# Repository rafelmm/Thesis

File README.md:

# Thesis
MERIT Thesis documents

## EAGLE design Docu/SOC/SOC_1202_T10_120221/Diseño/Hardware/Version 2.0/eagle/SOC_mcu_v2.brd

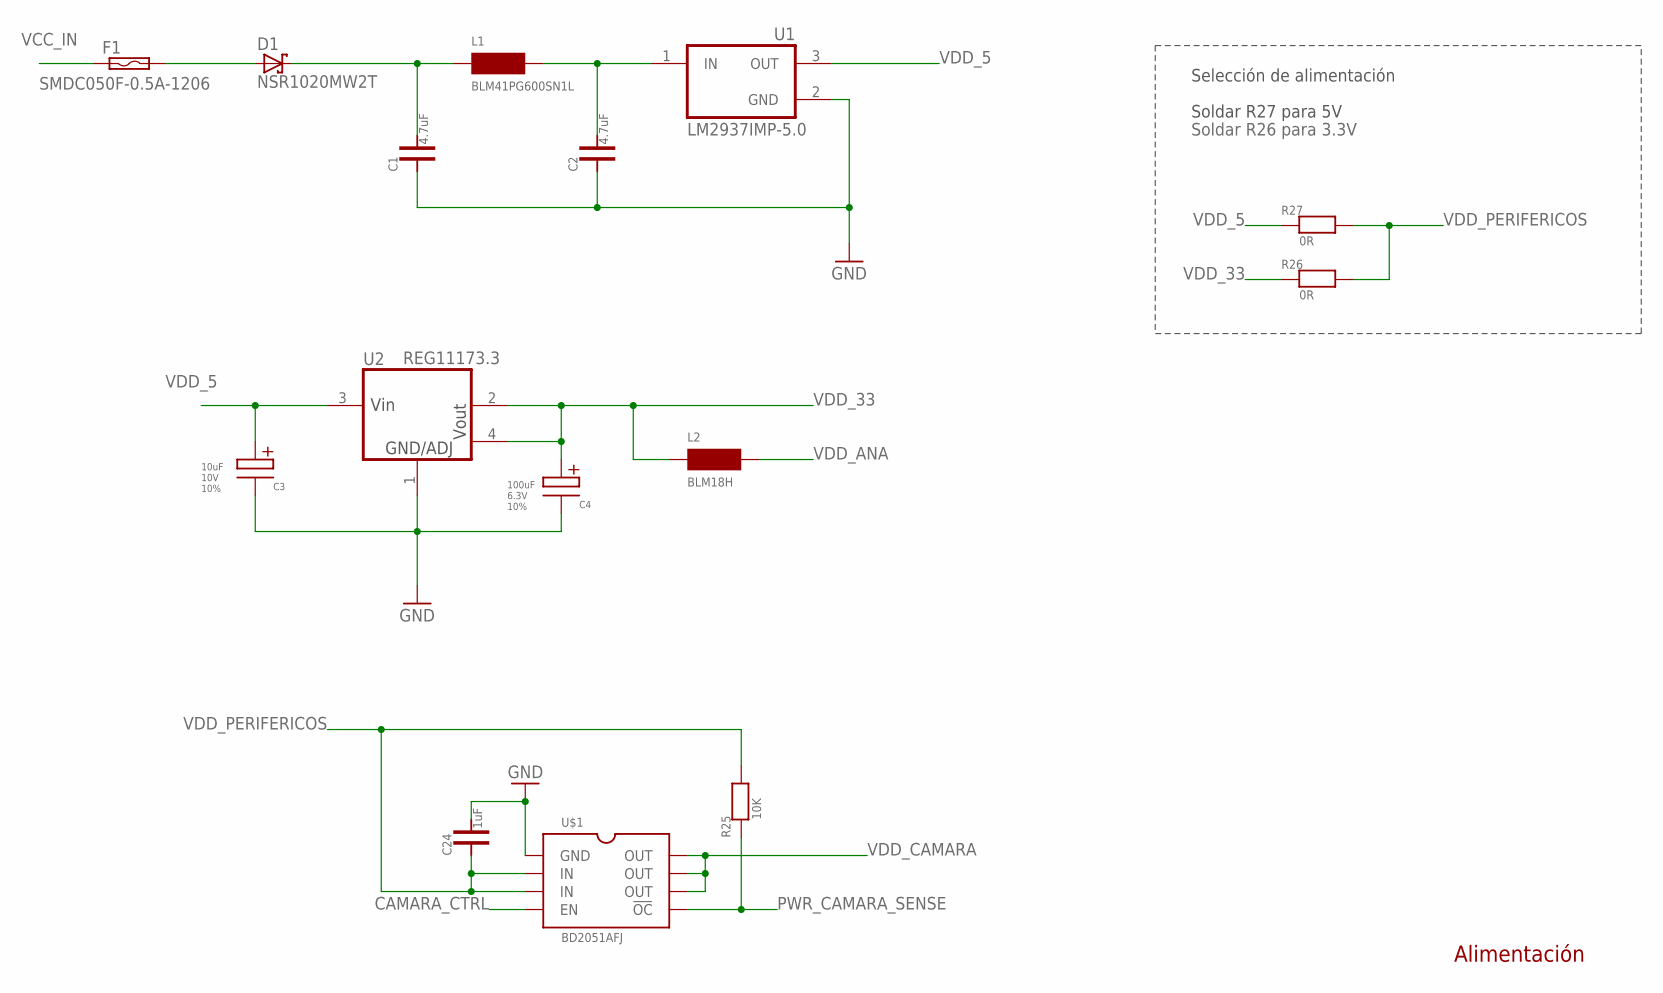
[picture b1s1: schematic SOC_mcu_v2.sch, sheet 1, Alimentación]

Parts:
C1, C2: 4.7uF; C0805
C3: 10uF; 3528-21
C4: 100uF; 3528-21
C24: 1uF; C0402
D1: NSR1020MW2T; SOD323
F1: SMDC050F-0.5A-1206; 1206; MPN NANOSMDC050F/13.2
L1: BLM41PG600SN1L; 1806
L2: BLM18H; 0603
R25: 10K; R0402
R26, R27: 0R; R0402
U1: LM2937IMP-5.0; SOT223
U2: REG11173.3; SOT223
U$1: BD2051AFJ; SO08

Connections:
CAMARA_CTRL: U$1.4 (EN); also elsewhere on the board
GND: C1.1, C2.1, C3.NEG, C4.NEG, C24.2, U1.2 (GND), U1.4 (GND), U2.1 (GND), U$1.1 (GND); also elsewhere on the board
unnamed: C2.2, L1.P$2 (2), U1.1 (IN)
unnamed: C1.2, D1.C, L1.P$1 (1)
unnamed: D1.A, F1.2
PWR_CAMARA_SENSE: R25.1, U$1.5 (!OC); also elsewhere on the board
VCC_IN: F1.1; also elsewhere on the board
VDD_5: C3.POS, R27.1, U1.3 (OUT), U2.3 (VIN)
VDD_33: C4.POS, L2.1, R26.1, U2.2 (VOUT), U2.4 (VO2); also elsewhere on the board
VDD_ANA: L2.2; also elsewhere on the board
VDD_CAMARA: U$1.6 (OUT), U$1.7 (OUT), U$1.8 (OUT); also elsewhere on the board
VDD_PERIFERICOS: C24.1, R25.2, R26.2, R27.2, U$1.2 (IN), U$1.3 (IN); also elsewhere on the board

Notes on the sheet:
Alimentación
Selección de alimentación
Soldar R27 para 5V
Soldar R26 para 3.3V

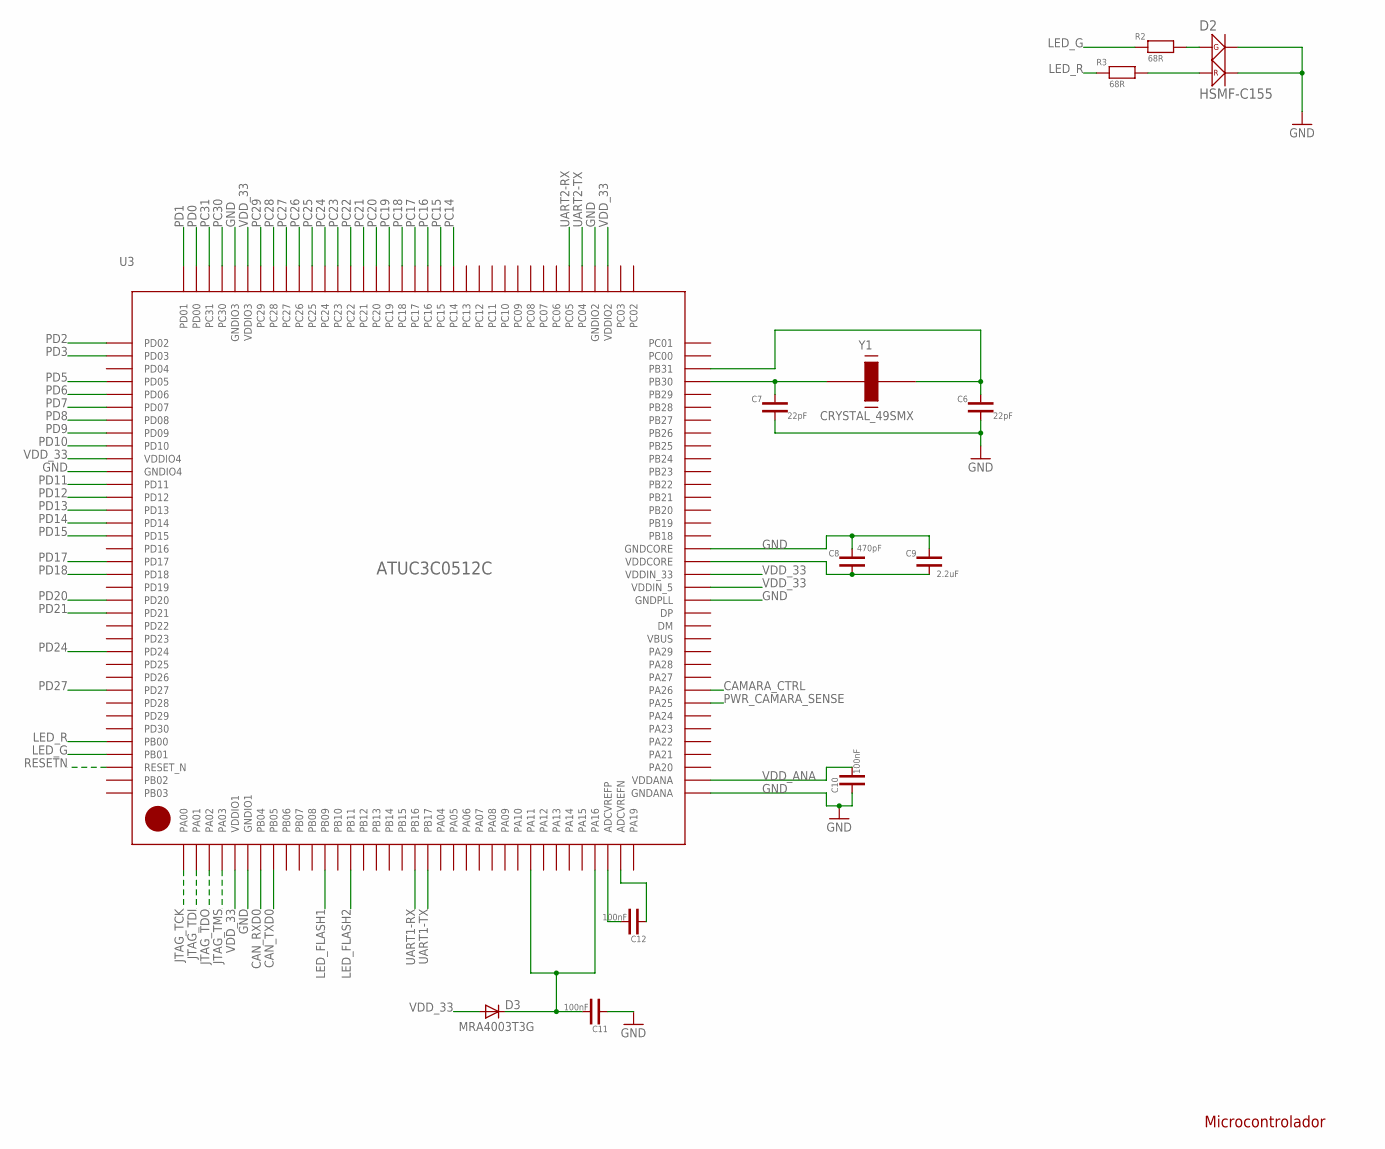
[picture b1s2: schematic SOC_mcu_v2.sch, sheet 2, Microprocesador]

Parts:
C6, C7: 22pF; C0402
C8: 470pF; C0402
C9: 2.2uF; C0603
C10, C11, C12: 100nF; C0402
D2: HSMF-C155; HSMF-C
D3: MRA4003T3G; SMA
R2, R3: 68R; R0402
U3: ATUC3C0512C; TQFP144
Y1: CRYSTAL_49SMX; HC49UP

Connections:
CAMARA_CTRL: U3.45 (PA26); also elsewhere on the board
CAN_RXD0: U3.7 (PB04); also elsewhere on the board
CAN_TXD0: U3.8 (PB05); also elsewhere on the board
GND: C6.1, C7.1, C8.2, C9.2, C10.1, C11.1, D2.2, D2.4, U3.6 (GNDIO1), U3.37 (GNDANA), U3.52 (GNDPLL), U3.56 (GNDCORE), U3.76 (GNDIO2), U3.104 (GNDIO3), U3.119 (GNDIO4); also elsewhere on the board
JTAG_TCK: U3.1 (PA00); also elsewhere on the board
JTAG_TDI: U3.2 (PA01); also elsewhere on the board
JTAG_TDO: U3.3 (PA02); also elsewhere on the board
JTAG_TMS: U3.4 (PA03); also elsewhere on the board
LED_FLASH1: U3.12 (PB09); also elsewhere on the board
LED_FLASH2: U3.14 (PB11); also elsewhere on the board
LED_G: R2.1, U3.141 (PB01)
LED_R: R3.1, U3.140 (PB00)
unnamed: C6.2, U3.70 (PB31), Y1.2
unnamed: C7.2, U3.69 (PB30), Y1.1
unnamed: C8.1, C9.1, U3.55 (VDDCORE)
unnamed: D2.1, R2.2
unnamed: D2.3, R3.2
unnamed: C11.2, D3.C, U3.28 (PA11), U3.33 (PA16)
unnamed: C12.2, U3.34 (ADCVREFP)
unnamed: C12.1, U3.35 (ADCVREFN)
PC14: U3.87 (PC14); also elsewhere on the board
PC15: U3.88 (PC15); also elsewhere on the board
PC16: U3.89 (PC16); also elsewhere on the board
PC17: U3.90 (PC17); also elsewhere on the board
PC18: U3.91 (PC18); also elsewhere on the board
PC19: U3.92 (PC19); also elsewhere on the board
PC20: U3.93 (PC20); also elsewhere on the board
PC21: U3.94 (PC21); also elsewhere on the board
PC22: U3.95 (PC22); also elsewhere on the board
PC23: U3.96 (PC23); also elsewhere on the board
PC24: U3.97 (PC24); also elsewhere on the board
PC25: U3.98 (PC25); also elsewhere on the board
PC26: U3.99 (PC26); also elsewhere on the board
PC27: U3.100 (PC27); also elsewhere on the board
PC28: U3.101 (PC28); also elsewhere on the board
PC29: U3.102 (PC29); also elsewhere on the board
PC30: U3.105 (PC30); also elsewhere on the board
PC31: U3.106 (PC31); also elsewhere on the board
PD0: U3.107 (PD00); also elsewhere on the board
PD1: U3.108 (PD01); also elsewhere on the board
PD2: U3.109 (PD02); also elsewhere on the board
PD3: U3.110 (PD03); also elsewhere on the board
PD5: U3.112 (PD05); also elsewhere on the board
PD6: U3.113 (PD06); also elsewhere on the board
PD7: U3.114 (PD07); also elsewhere on the board
PD8: U3.115 (PD08); also elsewhere on the board
PD9: U3.116 (PD09); also elsewhere on the board
PD10: U3.117 (PD10); also elsewhere on the board
PD11: U3.120 (PD11); also elsewhere on the board
PD12: U3.121 (PD12); also elsewhere on the board
PD13: U3.122 (PD13); also elsewhere on the board
PD14: U3.123 (PD14); also elsewhere on the board
PD15: U3.124 (PD15); also elsewhere on the board
PD17: U3.126 (PD17); also elsewhere on the board
PD18: U3.127 (PD18); also elsewhere on the board
PD20: U3.129 (PD20); also elsewhere on the board
PD21: U3.130 (PD21); also elsewhere on the board
PD24: U3.133 (PD24); also elsewhere on the board
PD27: U3.136 (PD27); also elsewhere on the board
PWR_CAMARA_SENSE: U3.44 (PA25); also elsewhere on the board
RESETN: U3.142 (RESET_N); also elsewhere on the board
UART1-RX: U3.19 (PB16); also elsewhere on the board
UART1-TX: U3.20 (PB17); also elsewhere on the board
UART2-RX: U3.78 (PC05); also elsewhere on the board
UART2-TX: U3.77 (PC04); also elsewhere on the board
VDD_33: D3.A, U3.5 (VDDIO1), U3.53 (VDDIN_5), U3.54 (VDDIN_33), U3.75 (VDDIO2), U3.103 (VDDIO3), U3.118 (VDDIO4); also elsewhere on the board
VDD_ANA: C10.2, U3.38 (VDDANA); also elsewhere on the board

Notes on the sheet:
Microcontrolador

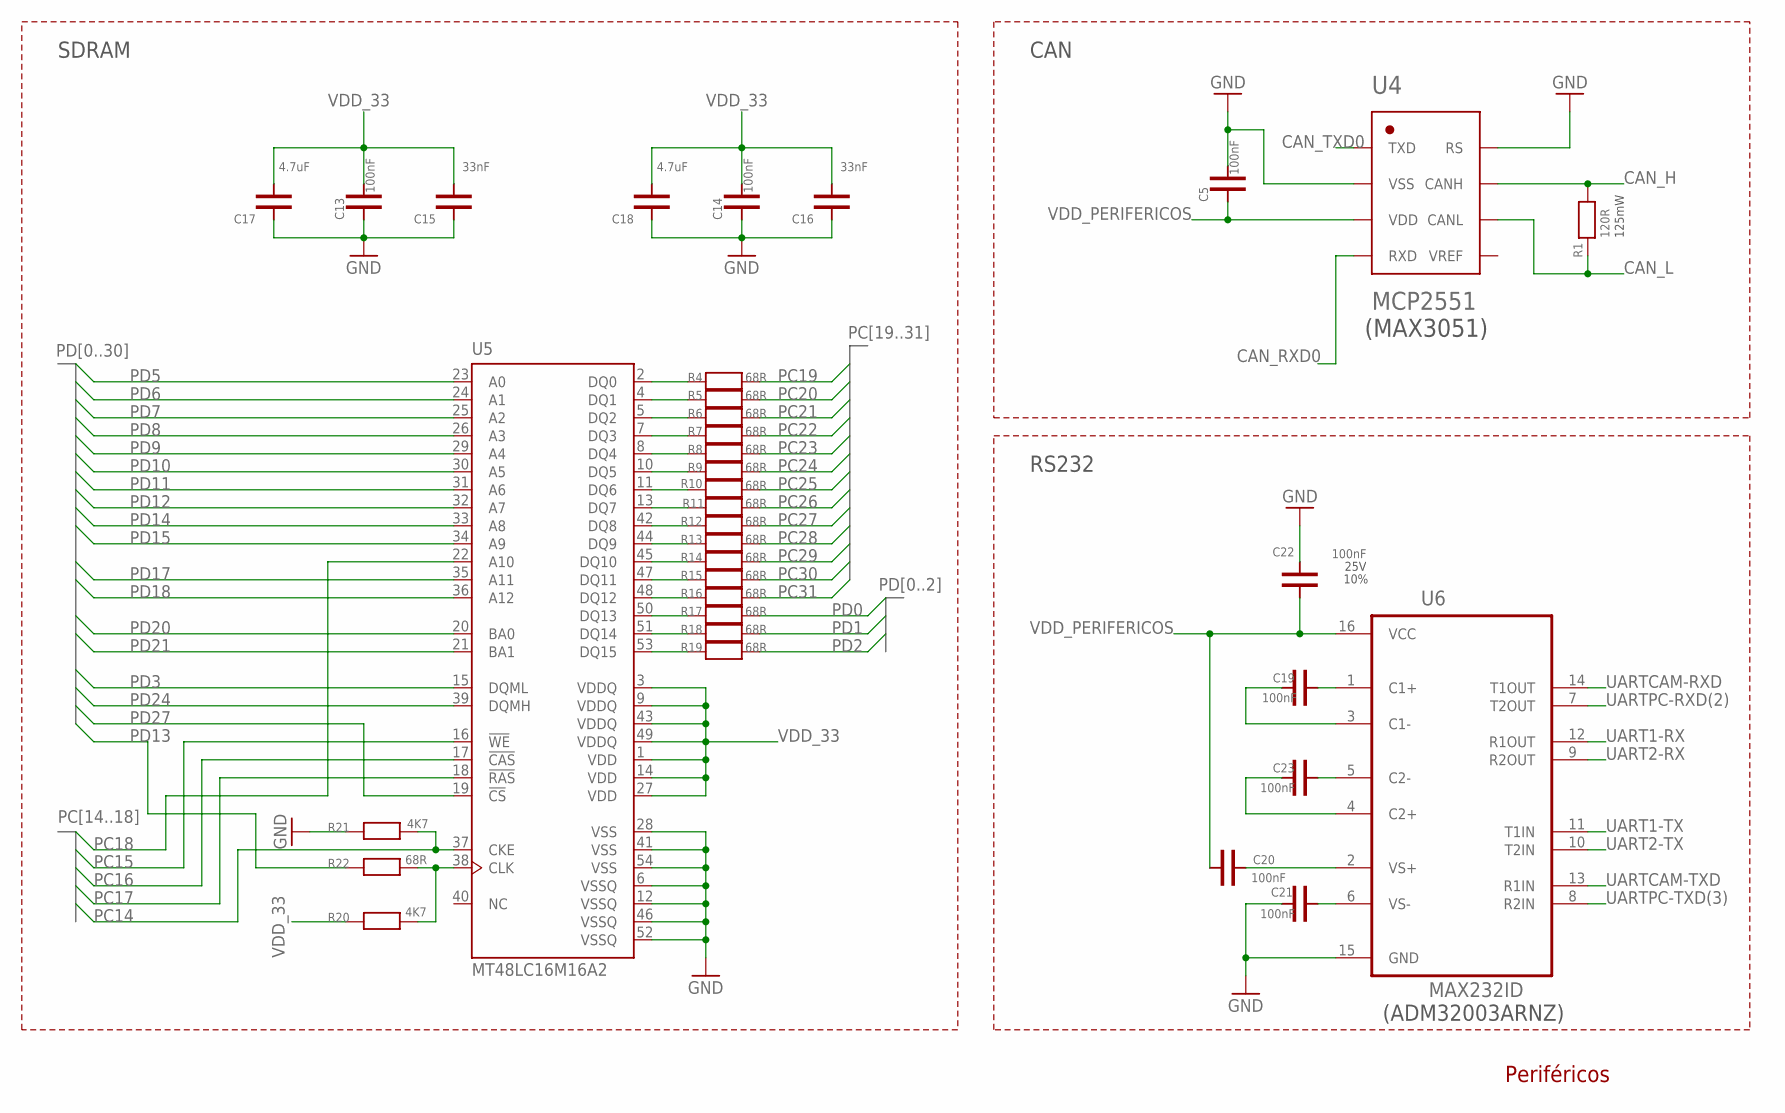
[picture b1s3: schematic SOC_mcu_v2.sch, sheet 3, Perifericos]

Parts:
C5, C13, C14: 100nF; C0402
C15, C16: 33nF; C0402; TOLERANCE 10%; VOLTAGE 25V
C17, C18: 4.7uF; C0805; TOLERANCE 10%; VOLTAGE 16V
C19, C20, C21, C22, C23: 100nF; C0402; TOLERANCE 10%; VOLTAGE 25V
R1: 120R; R0402; TOLERANCE 1%
R4, R5, R6, R7, R8, R9, R10, R11, R12, R13, R14, R15, R16, R17, R18, R19, R22: 68R; R0402; TOLERANCE 5%
R20, R21: 4K7; R0402; TOLERANCE 1%
U4: MCP2551; SO08
U5: MT48LC16M16A2; TSOP54-400
U6: MAX232ID; SOIC127P600X175-16N

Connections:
CAN_H: R1.2, U4.7 (CANH); also elsewhere on the board
CAN_L: R1.1, U4.6 (CANL); also elsewhere on the board
CAN_RXD0: U4.4 (RXD); also elsewhere on the board
CAN_TXD0: U4.1 (TXD); also elsewhere on the board
GND: C5.2, C13.1, C14.1, C15.1, C16.1, C17.1, C18.1, C21.1, C22.2, R21.1, U4.2 (VSS), U4.8 (RS), U5.6 (VSSQ), U5.12 (VSSQ), U5.28 (VSS), U5.41 (VSS), U5.46 (VSSQ), U5.52 (VSSQ), U5.54 (VSS), U6.15 (GND); also elsewhere on the board
unnamed: R4.1, U5.2 (DQ0)
unnamed: R5.1, U5.4 (DQ1)
unnamed: R6.1, U5.5 (DQ2)
unnamed: R7.1, U5.7 (DQ3)
unnamed: R8.1, U5.8 (DQ4)
unnamed: R9.1, U5.10 (DQ5)
unnamed: C19.2, U6.1 (C1+)
unnamed: R10.1, U5.11 (DQ6)
unnamed: R11.1, U5.13 (DQ7)
unnamed: R12.1, U5.42 (DQ8)
unnamed: R13.1, U5.44 (DQ9)
unnamed: R14.1, U5.45 (DQ10)
unnamed: R15.1, U5.47 (DQ11)
unnamed: R16.1, U5.48 (DQ12)
unnamed: R17.1, U5.50 (DQ13)
unnamed: R18.1, U5.51 (DQ14)
unnamed: R19.1, U5.53 (DQ15)
unnamed: R20.2, R22.2, U5.38 (CLK)
unnamed: C23.2, U6.5 (C2-)
unnamed: C19.1, U6.3 (C1-)
unnamed: C20.2, U6.2 (VS+)
unnamed: C23.1, U6.4 (C2+)
unnamed: C21.2, U6.6 (VS-)
PC14: R21.2, U5.37 (CKE); also elsewhere on the board
PC15: U5.16 (!WE); also elsewhere on the board
PC16: U5.17 (!CAS); also elsewhere on the board
PC17: U5.18 (!RAS); also elsewhere on the board
PC18: U5.22 (A10); also elsewhere on the board
PC19: R4.2; also elsewhere on the board
PC20: R5.2; also elsewhere on the board
PC21: R6.2; also elsewhere on the board
PC22: R7.2; also elsewhere on the board
PC23: R8.2; also elsewhere on the board
PC24: R9.2; also elsewhere on the board
PC25: R10.2; also elsewhere on the board
PC26: R11.2; also elsewhere on the board
PC27: R12.2; also elsewhere on the board
PC28: R13.2; also elsewhere on the board
PC29: R14.2; also elsewhere on the board
PC30: R15.2; also elsewhere on the board
PC31: R16.2; also elsewhere on the board
PD0: R17.2; also elsewhere on the board
PD1: R18.2; also elsewhere on the board
PD2: R19.2; also elsewhere on the board
PD3: U5.15 (DQML); also elsewhere on the board
PD5: U5.23 (A0); also elsewhere on the board
PD6: U5.24 (A1); also elsewhere on the board
PD7: U5.25 (A2); also elsewhere on the board
PD8: U5.26 (A3); also elsewhere on the board
PD9: U5.29 (A4); also elsewhere on the board
PD10: U5.30 (A5); also elsewhere on the board
PD11: U5.31 (A6); also elsewhere on the board
PD12: U5.32 (A7); also elsewhere on the board
PD13: R22.1; also elsewhere on the board
PD14: U5.33 (A8); also elsewhere on the board
PD15: U5.34 (A9); also elsewhere on the board
PD17: U5.35 (A11); also elsewhere on the board
PD18: U5.36 (A12); also elsewhere on the board
PD20: U5.20 (BA0); also elsewhere on the board
PD21: U5.21 (BA1); also elsewhere on the board
PD24: U5.39 (DQMH); also elsewhere on the board
PD27: U5.19 (!CS); also elsewhere on the board
UART1-RX: U6.12 (R1OUT); also elsewhere on the board
UART1-TX: U6.11 (T1IN); also elsewhere on the board
UART2-RX: U6.9 (R2OUT); also elsewhere on the board
UART2-TX: U6.10 (T2IN); also elsewhere on the board
UARTCAM-RXD: U6.14 (T1OUT); also elsewhere on the board
UARTCAM-TXD: U6.13 (R1IN); also elsewhere on the board
UARTPC-RXD(2): U6.7 (T2OUT); also elsewhere on the board
UARTPC-TXD(3): U6.8 (R2IN); also elsewhere on the board
VDD_33: C13.2, C14.2, C15.2, C16.2, C17.2, C18.2, R20.1, U5.1 (VDD), U5.3 (VDDQ), U5.9 (VDDQ), U5.14 (VDD), U5.27 (VDD), U5.43 (VDDQ), U5.49 (VDDQ); also elsewhere on the board
VDD_PERIFERICOS: C5.1, C20.1, C22.1, U4.3 (VDD), U6.16 (VCC); also elsewhere on the board

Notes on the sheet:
CAN
RS232
Periféricos
SDRAM
(MAX3051)
(ADM32003ARNZ)

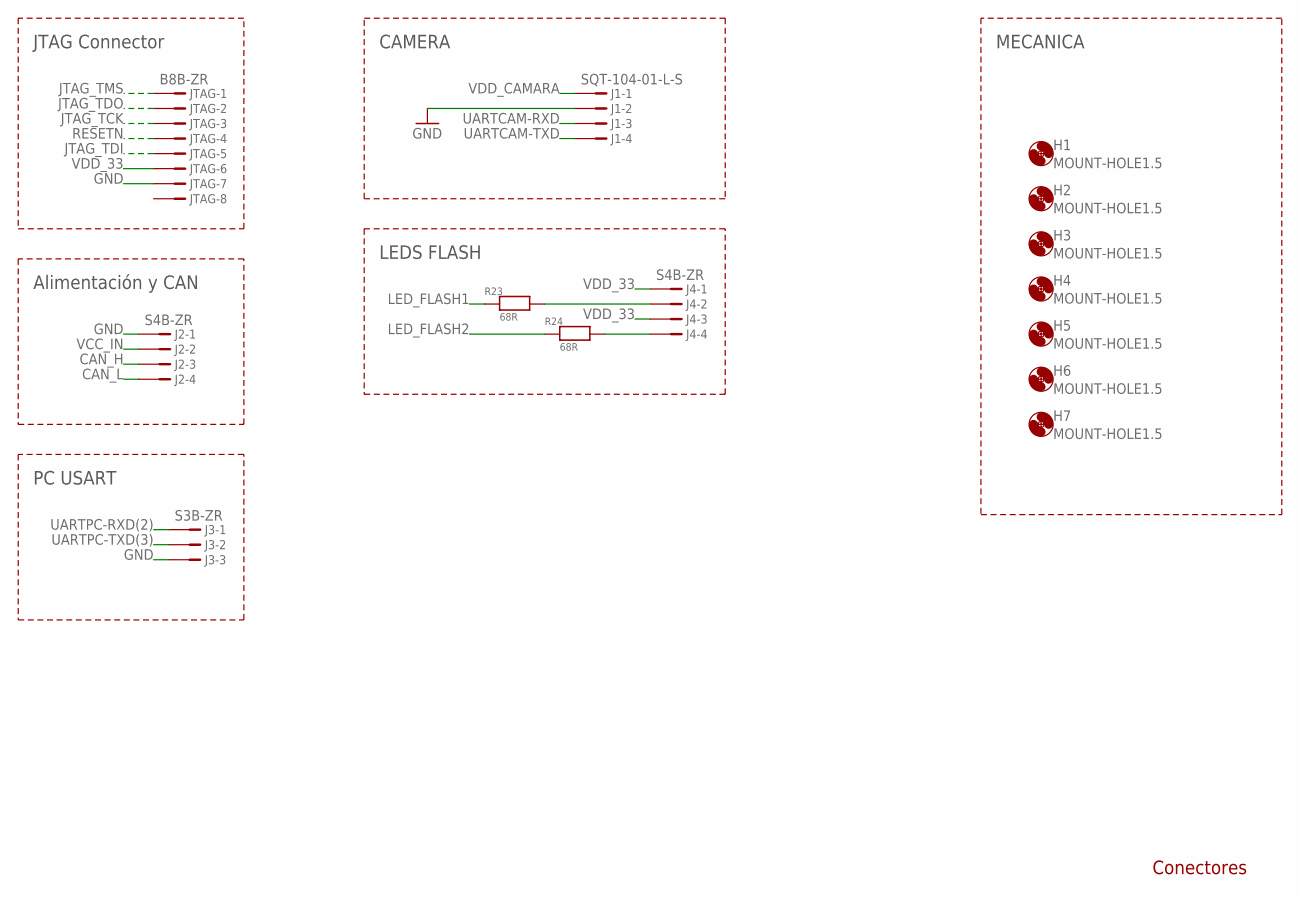
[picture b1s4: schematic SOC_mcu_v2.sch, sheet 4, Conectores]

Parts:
H1, H2, H3, H4, H5, H6, H7: MOUNT-HOLE1.5; 1,5
J1: SQT-104-01-L-S; THD-SQT-104-01-L-S
J2, J4: S4B-ZR
J3: S3B-ZR
JTAG: B8B-ZR
R23, R24: 68R; R0402

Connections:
CAN_H: J2.3; also elsewhere on the board
CAN_L: J2.4; also elsewhere on the board
GND: J1.2, J2.1, J3.3, JTAG.7; also elsewhere on the board
JTAG_TCK: JTAG.3; also elsewhere on the board
JTAG_TDI: JTAG.5; also elsewhere on the board
JTAG_TDO: JTAG.2; also elsewhere on the board
JTAG_TMS: JTAG.1; also elsewhere on the board
LED_FLASH1: R23.1; also elsewhere on the board
LED_FLASH2: R24.1; also elsewhere on the board
unnamed: J4.2, R23.2
unnamed: J4.4, R24.2
RESETN: JTAG.4; also elsewhere on the board
UARTCAM-RXD: J1.3; also elsewhere on the board
UARTCAM-TXD: J1.4; also elsewhere on the board
UARTPC-RXD(2): J3.1; also elsewhere on the board
UARTPC-TXD(3): J3.2; also elsewhere on the board
VCC_IN: J2.2; also elsewhere on the board
VDD_33: J4.1, J4.3, JTAG.6; also elsewhere on the board
VDD_CAMARA: J1.1; also elsewhere on the board

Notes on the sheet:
JTAG Connector
Conectores
Alimentación y CAN
PC USART
CAMERA
LEDS FLASH
MECANICA

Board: 2 copper layers, 77 parts (31 on the bottom side), 105 nets, no tracks yet.

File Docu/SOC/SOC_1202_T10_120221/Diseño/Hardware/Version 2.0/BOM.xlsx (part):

Componente | Simbolo | Valor | Unidades | Farnell | RS | Otro | Precio | Cantidad | total
Resistor | R23, R24, R25, R26, R27, R28 | 0R | ohms | 2073956 |  |  | 8.9999999999999993E-3 | 6 | 5.3999999999999992E-2 |  | TOTAL | 44.965999999999994
 | C19, C20, C21, C22, C23 | 100nF | nF | 1867948 | 723-5174 |  | 9.0999999999999998E-2 | 5 | 0.45499999999999996
 | C5, C10, C11, C12, C13, C14 | 100nF | nF | 1327657 | 698-3162 |  | 6.6000000000000003E-2 | 6 | 0.39600000000000002 |  | Componentes | 73
Condensador | C4 | 100uF | uF | 1754153 | 684-3932 |  | 0.26 | 1 | 0.26
Condensador | C3 | 10uF | uF | 1754163 | 684-3888 |  | 0.24 | 1 | 0.24
Resistor | R1 | 120R | ohms | 1738838 | - |  | 2.9000000000000001E-2 | 1 | 2.9000000000000001E-2
 | C9 | 2.2uF | uF | 1458901 | - |  | 8.5000000000000006E-2 | 1 | 8.5000000000000006E-2
 | C6, C7 | 22pF | pF | 8819629 | 624-2187 |  | 2.1000000000000001E-2 | 2 | 4.2000000000000003E-2
 | C15, C16 | 33nF | nF | 1865445 | - |  | 0 | 2 | 0
 | C1, C2, C17, C18 | 4.7uF | uF | 1845746 |  |  | 1.7000000000000001E-2 | 4 | 6.8000000000000005E-2
 | C8 | 470pF | pF | 1414593 | - |  | 2.1000000000000001E-2 | 1 | 2.1000000000000001E-2
Resistor | R20, R21 | 4K7 | Kohms | 1738858 | - |  | 2.9000000000000001E-2 | 2 | 5.8000000000000003E-2
Resistor | R2, R3, R4, R5, R6, R7, R8, R9, R10, R11, R12, R13, R14, R15, R16, R17, R18, R1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 | 68R | ohms | 1739078 | 678-9535 |  | 1.0999999999999999E-2 | 21 | 0.23099999999999998
ATUC3C0512C | U3 | ATUC3C0512C |  | 1972028 | 738-0120 |  | 19.54 | 1 | 19.54
Ferrita | L2 | BLM18H |  | 1515733 | 724-1378 |  | 0.14799999999999999 | 1 | 0.14799999999999999
Ferrita BLM41PG600SN1L | L1 | BLM41PG600SN1L |  | 9526900 | 188-8665 |  | 0.23899999999999999 | 1 | 0.23899999999999999
Crystal | Y1 | CRYSTAL_49SMX |  | 1640900 |  |  | 2.16 | 1 | 2.16
Led bicolor Rojo y Verde | D2 | HSMF-C155 |  | 5790888 | 486-0430 |  | 0.17799999999999999 | 1 | 0.17799999999999999
400 and 500 mA Low Dropout Voltage Regulator | U1 | LM2937IMP-5.0 |  | 1798318 | 761-5609 |  | 1.296 | 1 | 1.296
DUAL EIA-232 DRIVERS/ RECEIVERS | U6 | MAX232ID |  | 9589791 |  |  | 0.78 | 1 | 0.78
CAN Transciever | U4 | MCP2551 |  | 1467746 |  |  | 1.37 | 1 | 1.37
DIODE | D3 | MRA4003T3G |  | 1459134 | 545-2434 |  | 0.33 | 1 | 0.33
256Mb: x16 SDRAM MT48LC16M16A2 - 4 Meg x 16 x 4 banks | U5 | MT48LC16M16A2 |  | 1216281 |  |  | 13.4 | 1 | 13.4
Diodo Schottky | D1 | NSR1020MW2T |  | 1431027 | - |  | 0.18 | 1 | 0.18
800mA and 1A Low Dropout (LDO) Positive Regulator | U2 | REG11173.3 | V | 1494942 | 660-7975 |  | 0.25 | 1 | 0.25
S4B-ZR | J2, J4 | S4B-ZR |  | 9491830 |  |  | 0.47 | 2 | 0.94
PolySwitch (TM) Resettable Device | F1 | SMDC050F-0.5A-1206 |  | 1345942 | 138-679 |  | 0.54 | 1 | 0.54
Receptaculo 4 vias | J1 | SQT-104-01-L-S |  | 1668155 |  |  | 1.43 | 1 | 1.43
ZHR-3 | J3 | Connector Socket |  | 3357557 |  |  | 4.5999999999999999E-2 | 3 | 0.13800000000000001
ZHR-8 |  | Connector Socket |  | 1830900 |  |  | 0.108 | 1 | 0.108
 |  |  |  |  |  |  |  |  | 0
 |  |  |  |  |  |  |  |  | 0
 |  |  |  |  |  |  |  |  | 0
 |  |  |  |  |  |  |  |  | 0
 |  |  |  |  |  |  |  |  | 0
 |  |  |  |  |  |  |  |  | 0
 |  |  |  |  |  |  |  |  | 0
 |  |  |  |  |  |  |  |  | 0
 |  |  |  |  |  |  |  |  | 0
 |  |  |  |  |  |  |  |  | 0
 |  |  |  |  |  |  |  |  | 0
 |  |  |  |  |  |  |  |  | 0
 |  |  |  |  |  |  |  |  | 0
 |  |  |  |  |  |  |  |  | 0
 |  |  |  |  |  |  |  |  | 0
 |  |  |  |  |  |  |  |  | 0
 |  |  |  |  |  |  |  |  | 0
 |  |  |  |  |  |  |  |  | 0
 |  |  |  |  |  |  |  |  | 0
 |  |  |  |  |  |  |  |  | 0
 |  |  |  |  |  |  |  |  | 0
 |  |  |  |  |  |  |  |  | 0
 |  |  |  |  |  |  |  |  | 0
 |  |  |  |  |  |  |  |  | 0
 |  |  |  |  |  |  |  |  | 0
 |  |  |  |  |  |  |  |  | 0
 |  |  |  |  |  |  |  |  | 0
 |  |  |  |  |  |  |  |  | 0
 |  |  |  |  |  |  |  |  | 0
 |  |  |  |  |  |  |  |  | 0
 |  |  |  |  |  |  |  |  | 0
 |  |  |  |  |  |  |  |  | 0
 |  |  |  |  |  |  |  |  | 0
 |  |  |  |  |  |  |  |  | 0
 |  |  |  |  |  |  |  |  | 0
 |  |  |  |  |  |  |  |  | 0
 |  |  |  |  |  |  |  |  | 0
 |  |  |  |  |  |  |  |  | 0
 |  |  |  |  |  |  |  |  | 0
 |  |  |  |  |  |  |  |  | 0
 |  |  |  |  |  |  |  |  | 0
 |  |  |  |  |  |  |  |  | 0
 |  |  |  |  |  |  |  |  | 0
 |  |  |  |  |  |  |  |  | 0
 |  |  |  |  |  |  |  |  | 0
 |  |  |  |  |  |  |  |  | 0
 |  |  |  |  |  |  |  |  | 0
 |  |  |  |  |  |  |  |  | 0
 |  |  |  |  |  |  |  |  | 0
 |  |  |  |  |  |  |  |  | 0
 |  |  |  |  |  |  |  |  | 0
 |  |  |  |  |  |  |  |  | 0
 |  |  |  |  |  |  |  |  | 0
 |  |  |  |  |  |  |  |  | 0
 |  |  |  |  |  |  |  |  | 0
 |  |  |  |  |  |  |  |  | 0
 |  |  |  |  |  |  |  |  | 0
 |  |  |  |  |  |  |  |  | 0
 |  |  |  |  |  |  |  |  | 0
 |  |  |  |  |  |  |  |  | 0
 |  |  |  |  |  |  |  |  | 0
 |  |  |  |  |  |  |  |  | 0
 |  |  |  |  |  |  |  |  | 0
 |  |  |  |  |  |  |  |  | 0
 |  |  |  |  |  |  |  |  | 0
 |  |  |  |  |  |  |  |  | 0
 |  |  |  |  |  |  |  |  | 0
 |  |  |  |  |  |  |  |  | 0
 |  |  |  |  |  |  |  |  | 0
 |  |  |  |  |  |  |  |  | 0
 |  |  |  |  |  |  |  |  | 0
 |  |  |  |  |  |  |  |  | 0
 |  |  |  |  |  |  |  |  | 0
 |  |  |  |  |  |  |  |  | 0
 |  |  |  |  |  |  |  |  | 0
 |  |  |  |  |  |  |  |  | 0
 |  |  |  |  |  |  |  |  | 0
 |  |  |  |  |  |  |  |  | 0
 |  |  |  |  |  |  |  |  | 0
 |  |  |  |  |  |  |  |  | 0
 |  |  |  |  |  |  |  |  | 0
 |  |  |  |  |  |  |  |  | 0
 |  |  |  |  |  |  |  |  | 0
 |  |  |  |  |  |  |  |  | 0
 |  |  |  |  |  |  |  |  | 0
 |  |  |  |  |  |  |  |  | 0
 |  |  |  |  |  |  |  |  | 0
 |  |  |  |  |  |  |  |  | 0
 |  |  |  |  |  |  |  |  | 0
 |  |  |  |  |  |  |  |  | 0
 |  |  |  |  |  |  |  |  | 0
 |  |  |  |  |  |  |  |  | 0
 |  |  |  |  |  |  |  |  | 0
 |  |  |  |  |  |  |  |  | 0
 |  |  |  |  |  |  |  |  | 0
 |  |  |  |  |  |  |  |  | 0
 |  |  |  |  |  |  |  |  | 0
 |  |  |  |  |  |  |  |  | 0
 |  |  |  |  |  |  |  |  | 0
 |  |  |  |  |  |  |  |  | 0
 |  |  |  |  |  |  |  |  | 0
 |  |  |  |  |  |  |  |  | 0
 |  |  |  |  |  |  |  |  | 0
 |  |  |  |  |  |  |  |  | 0
 |  |  |  |  |  |  |  |  | 0
 |  |  |  |  |  |  |  |  | 0
 |  |  |  |  |  |  |  |  | 0
 |  |  |  |  |  |  |  |  | 0
 |  |  |  |  |  |  |  |  | 0
 |  |  |  |  |  |  |  |  | 0
 |  |  |  |  |  |  |  |  | 0
 |  |  |  |  |  |  |  |  | 0
 |  |  |  |  |  |  |  |  | 0
 |  |  |  |  |  |  |  |  | 0
 |  |  |  |  |  |  |  |  | 0
 |  |  |  |  |  |  |  |  | 0
 |  |  |  |  |  |  |  |  | 0
 |  |  |  |  |  |  |  |  | 0
 |  |  |  |  |  |  |  |  | 0
 |  |  |  |  |  |  |  |  | 0
 |  |  |  |  |  |  |  |  | 0
 |  |  |  |  |  |  |  |  | 0
 |  |  |  |  |  |  |  |  | 0
 |  |  |  |  |  |  |  |  | 0
 |  |  |  |  |  |  |  |  | 0
 |  |  |  |  |  |  |  |  | 0
 |  |  |  |  |  |  |  |  | 0
 |  |  |  |  |  |  |  |  | 0
 |  |  |  |  |  |  |  |  | 0
 |  |  |  |  |  |  |  |  | 0
 |  |  |  |  |  |  |  |  | 0
 |  |  |  |  |  |  |  |  | 0
 |  |  |  |  |  |  |  |  | 0
 |  |  |  |  |  |  |  |  | 0
 |  |  |  |  |  |  |  |  | 0
 |  |  |  |  |  |  |  |  | 0
 |  |  |  |  |  |  |  |  | 0
 |  |  |  |  |  |  |  |  | 0
 |  |  |  |  |  |  |  |  | 0
 |  |  |  |  |  |  |  |  | 0
 |  |  |  |  |  |  |  |  | 0
 |  |  |  |  |  |  |  |  | 0
 |  |  |  |  |  |  |  |  | 0
 |  |  |  |  |  |  |  |  | 0
 |  |  |  |  |  |  |  |  | 0
 |  |  |  |  |  |  |  |  | 0
 |  |  |  |  |  |  |  |  | 0
 |  |  |  |  |  |  |  |  | 0
 |  |  |  |  |  |  |  |  | 0
 |  |  |  |  |  |  |  |  | 0
 |  |  |  |  |  |  |  |  | 0
 |  |  |  |  |  |  |  |  | 0
 |  |  |  |  |  |  |  |  | 0
 |  |  |  |  |  |  |  |  | 0
 |  |  |  |  |  |  |  |  | 0
 |  |  |  |  |  |  |  |  | 0
 |  |  |  |  |  |  |  |  | 0
 |  |  |  |  |  |  |  |  | 0
 |  |  |  |  |  |  |  |  | 0
 |  |  |  |  |  |  |  |  | 0
 |  |  |  |  |  |  |  |  | 0
 |  |  |  |  |  |  |  |  | 0
 |  |  |  |  |  |  |  |  | 0
 |  |  |  |  |  |  |  |  | 0
 |  |  |  |  |  |  |  |  | 0
 |  |  |  |  |  |  |  |  | 0
 |  |  |  |  |  |  |  |  | 0
 |  |  |  |  |  |  |  |  | 0
 |  |  |  |  |  |  |  |  | 0
 |  |  |  |  |  |  |  |  | 0
 |  |  |  |  |  |  |  |  | 0
 |  |  |  |  |  |  |  |  | 0
 |  |  |  |  |  |  |  |  | 0
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
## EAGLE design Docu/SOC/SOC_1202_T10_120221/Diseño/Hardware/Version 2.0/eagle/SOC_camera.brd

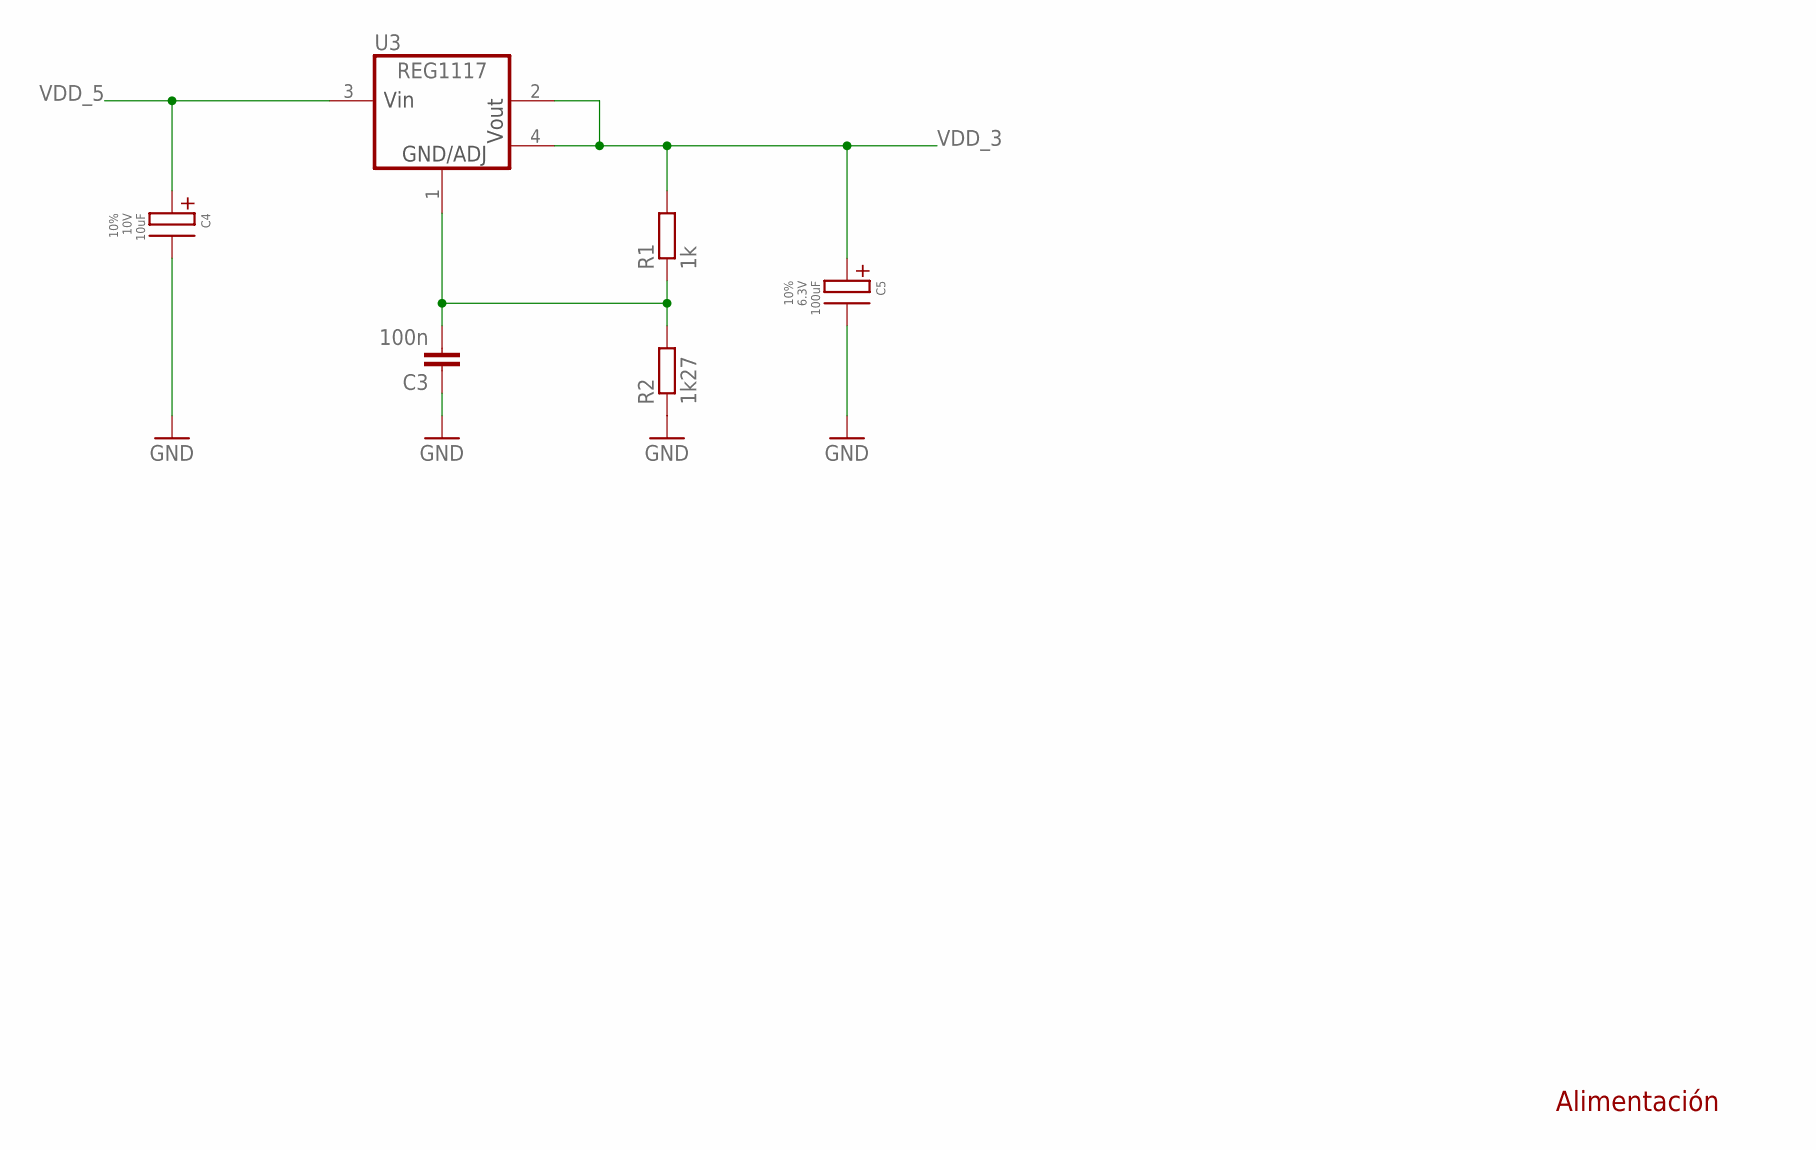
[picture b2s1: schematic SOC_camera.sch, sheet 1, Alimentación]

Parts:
C3: 100n; C0603
C4: 10uF; 3528-21
C5: 100uF; 3528-21
R1: 1k; R0603
R2: 1k27; R0603
U3: REG1117; SOT223

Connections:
GND: C3.1, C4.NEG, C5.NEG, R2.1; also elsewhere on the board
unnamed: C3.2, R1.1, R2.2, U3.1 (GND)
VDD_3: C5.POS, R1.2, U3.2 (VOUT), U3.4 (VO2); also elsewhere on the board
VDD_5: C4.POS, U3.3 (VIN); also elsewhere on the board

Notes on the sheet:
Alimentación

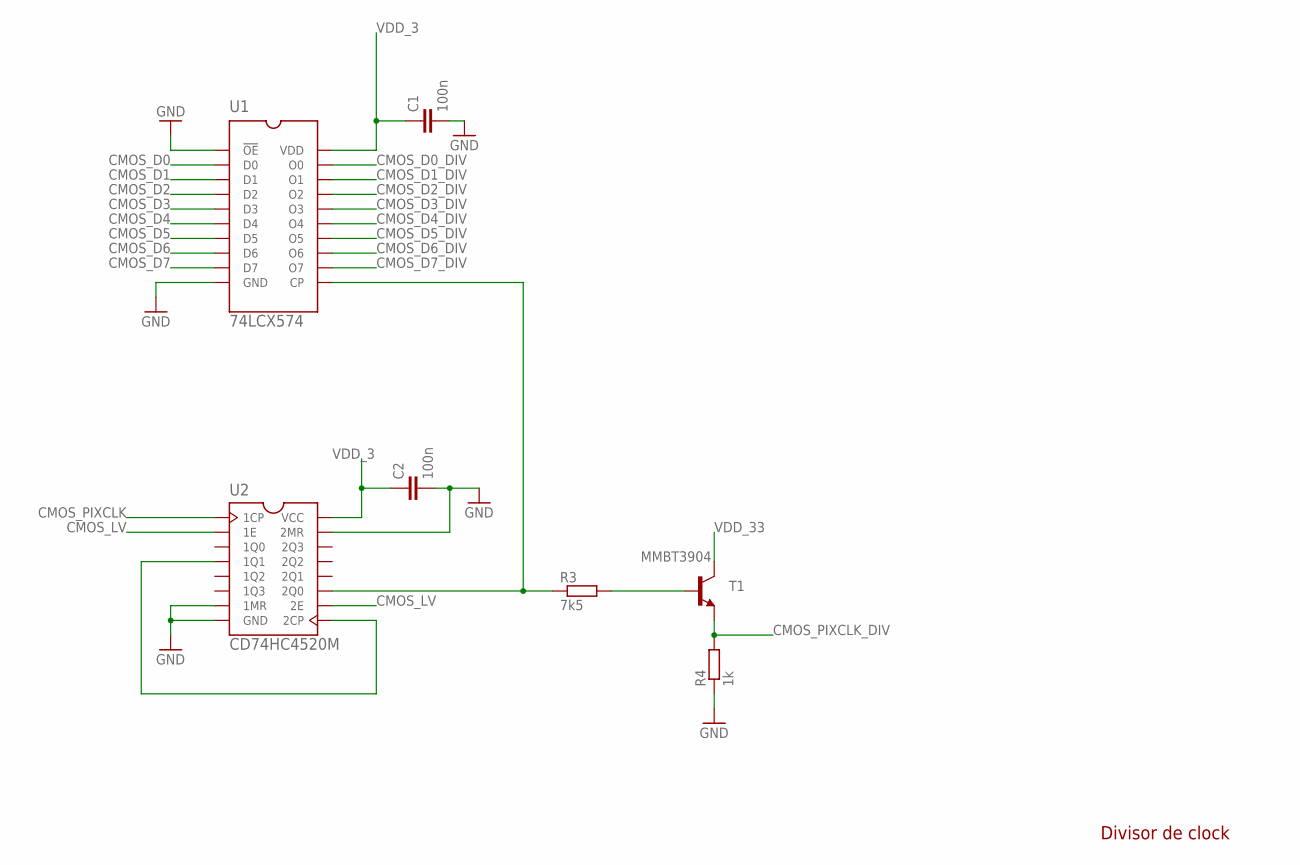
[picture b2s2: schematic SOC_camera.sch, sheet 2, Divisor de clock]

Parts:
C1, C2: 100n; C0603
R3: 7k5; R0603
R4: 1k; R0603
T1: MMBT3904; SOT23-BEC
U1: 74LCX574; TSSOP20
U2: CD74HC4520M; SOP16

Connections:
CMOS_D0: U1.2 (D0); also elsewhere on the board
CMOS_D0_DIV: U1.19 (O0); also elsewhere on the board
CMOS_D1: U1.3 (D1); also elsewhere on the board
CMOS_D1_DIV: U1.18 (O1); also elsewhere on the board
CMOS_D2: U1.4 (D2); also elsewhere on the board
CMOS_D2_DIV: U1.17 (O2); also elsewhere on the board
CMOS_D3: U1.5 (D3); also elsewhere on the board
CMOS_D3_DIV: U1.16 (O3); also elsewhere on the board
CMOS_D4: U1.6 (D4); also elsewhere on the board
CMOS_D4_DIV: U1.15 (O4); also elsewhere on the board
CMOS_D5: U1.7 (D5); also elsewhere on the board
CMOS_D5_DIV: U1.14 (O5); also elsewhere on the board
CMOS_D6: U1.8 (D6); also elsewhere on the board
CMOS_D6_DIV: U1.13 (O6); also elsewhere on the board
CMOS_D7: U1.9 (D7); also elsewhere on the board
CMOS_D7_DIV: U1.12 (O7); also elsewhere on the board
CMOS_LV: U2.2 (1E), U2.10 (2E); also elsewhere on the board
CMOS_PIXCLK: U2.1 (1CP); also elsewhere on the board
CMOS_PIXCLK_DIV: R4.2, T1.E; also elsewhere on the board
GND: C1.2, C2.2, R4.1, U1.1 (!OE), U1.10 (GND), U2.7 (1MR), U2.8 (GND), U2.15 (2MR); also elsewhere on the board
unnamed: U2.4 (1Q1), U2.9 (2CP)
unnamed: R3.2, T1.B
unnamed: R3.1, U1.11 (CP), U2.11 (2Q0)
VDD_3: C1.1, C2.1, U1.20 (VDD), U2.16 (VCC); also elsewhere on the board
VDD_33: T1.C; also elsewhere on the board

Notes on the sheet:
Divisor de clock
